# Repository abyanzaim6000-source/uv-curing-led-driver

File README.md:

# Dual-channel UV curing LED driver PCB

A 12 V constant-current driver with two independently PWM-controlled UV outputs. Rev C1 is a routed 110 × 76 mm, four-layer PCB using commercial TI TPS92691 controllers and external power stages. This project closes at the design and simulation stage. Hardware fabrication, measured performance, and curing validation are pending.

| Channel | Power stage | Rev C1 nominal current |
| --- | --- | ---: |
| 365 nm | SEPIC with a 1:1 coupled inductor | 579 mA |
| 405 nm | Boost with upstream TPS26630 eFuse | 501 mA |

*KiCad render. Parts without 3D models appear as footprints.*

## Design decisions

- The 365 nm supply and load voltage ranges call for step-up and step-down operation. Switched modeling showed a growing oscillation with separate inductors and supported selecting the coupled-inductor design.
- The 405 nm output targets a 32–34 V load. Its boost stage includes an eFuse to disconnect the input during a sustained fault.
- Rev C1 uses lower current settings for initial dummy-load bring-up. Modeling also supported increasing the 405 nm soft-start capacitor to 220 nF.

## Files and verification

- [KiCad project](uv_driver/rev_c/UV_DRIVER.kicad_pro), [schematic](uv_driver/rev_c/UV_DRIVER.kicad_sch), and [routed PCB](uv_driver/rev_c/UV_DRIVER.kicad_pcb)
- [Fabrication quote package](results/UV_DRIVER_RevC1_QUOTE_ONLY.zip) with Gerbers, drills, BOM, placements, and KiCad reports
- [Prototype engineering notes](docs/UV_REV_C1_PROTOTYPE.md) and [interview walkthrough](DEMO.md)

| Check | Result |
| --- | --- |
| KiCad 10.0.3 | Zero ERC or DRC violations, unrouted connections, or schematic-to-PCB mismatches |
| 365 nm switched stability screen | No growing mode in 128 modeled operating conditions |
| 405 nm nominal-current transient model | Up to 0.524 A at startup and 0.547 A at PWM restart |

From the project root, run the following with Python 3.9 or later. The SEPIC model requires NumPy.

    python3 scripts/check_uv_sepic_switching.py
    python3 scripts/check_uv_405_restart.py --prototype

The earlier [buck simulation study](docs/LEGACY_BUCK_STUDY.md) and the [development tracker](CODEX_PLAN.md) document the project history. The [bench worksheet](docs/UV_405_BENCH.md) records how the design can be tested later.

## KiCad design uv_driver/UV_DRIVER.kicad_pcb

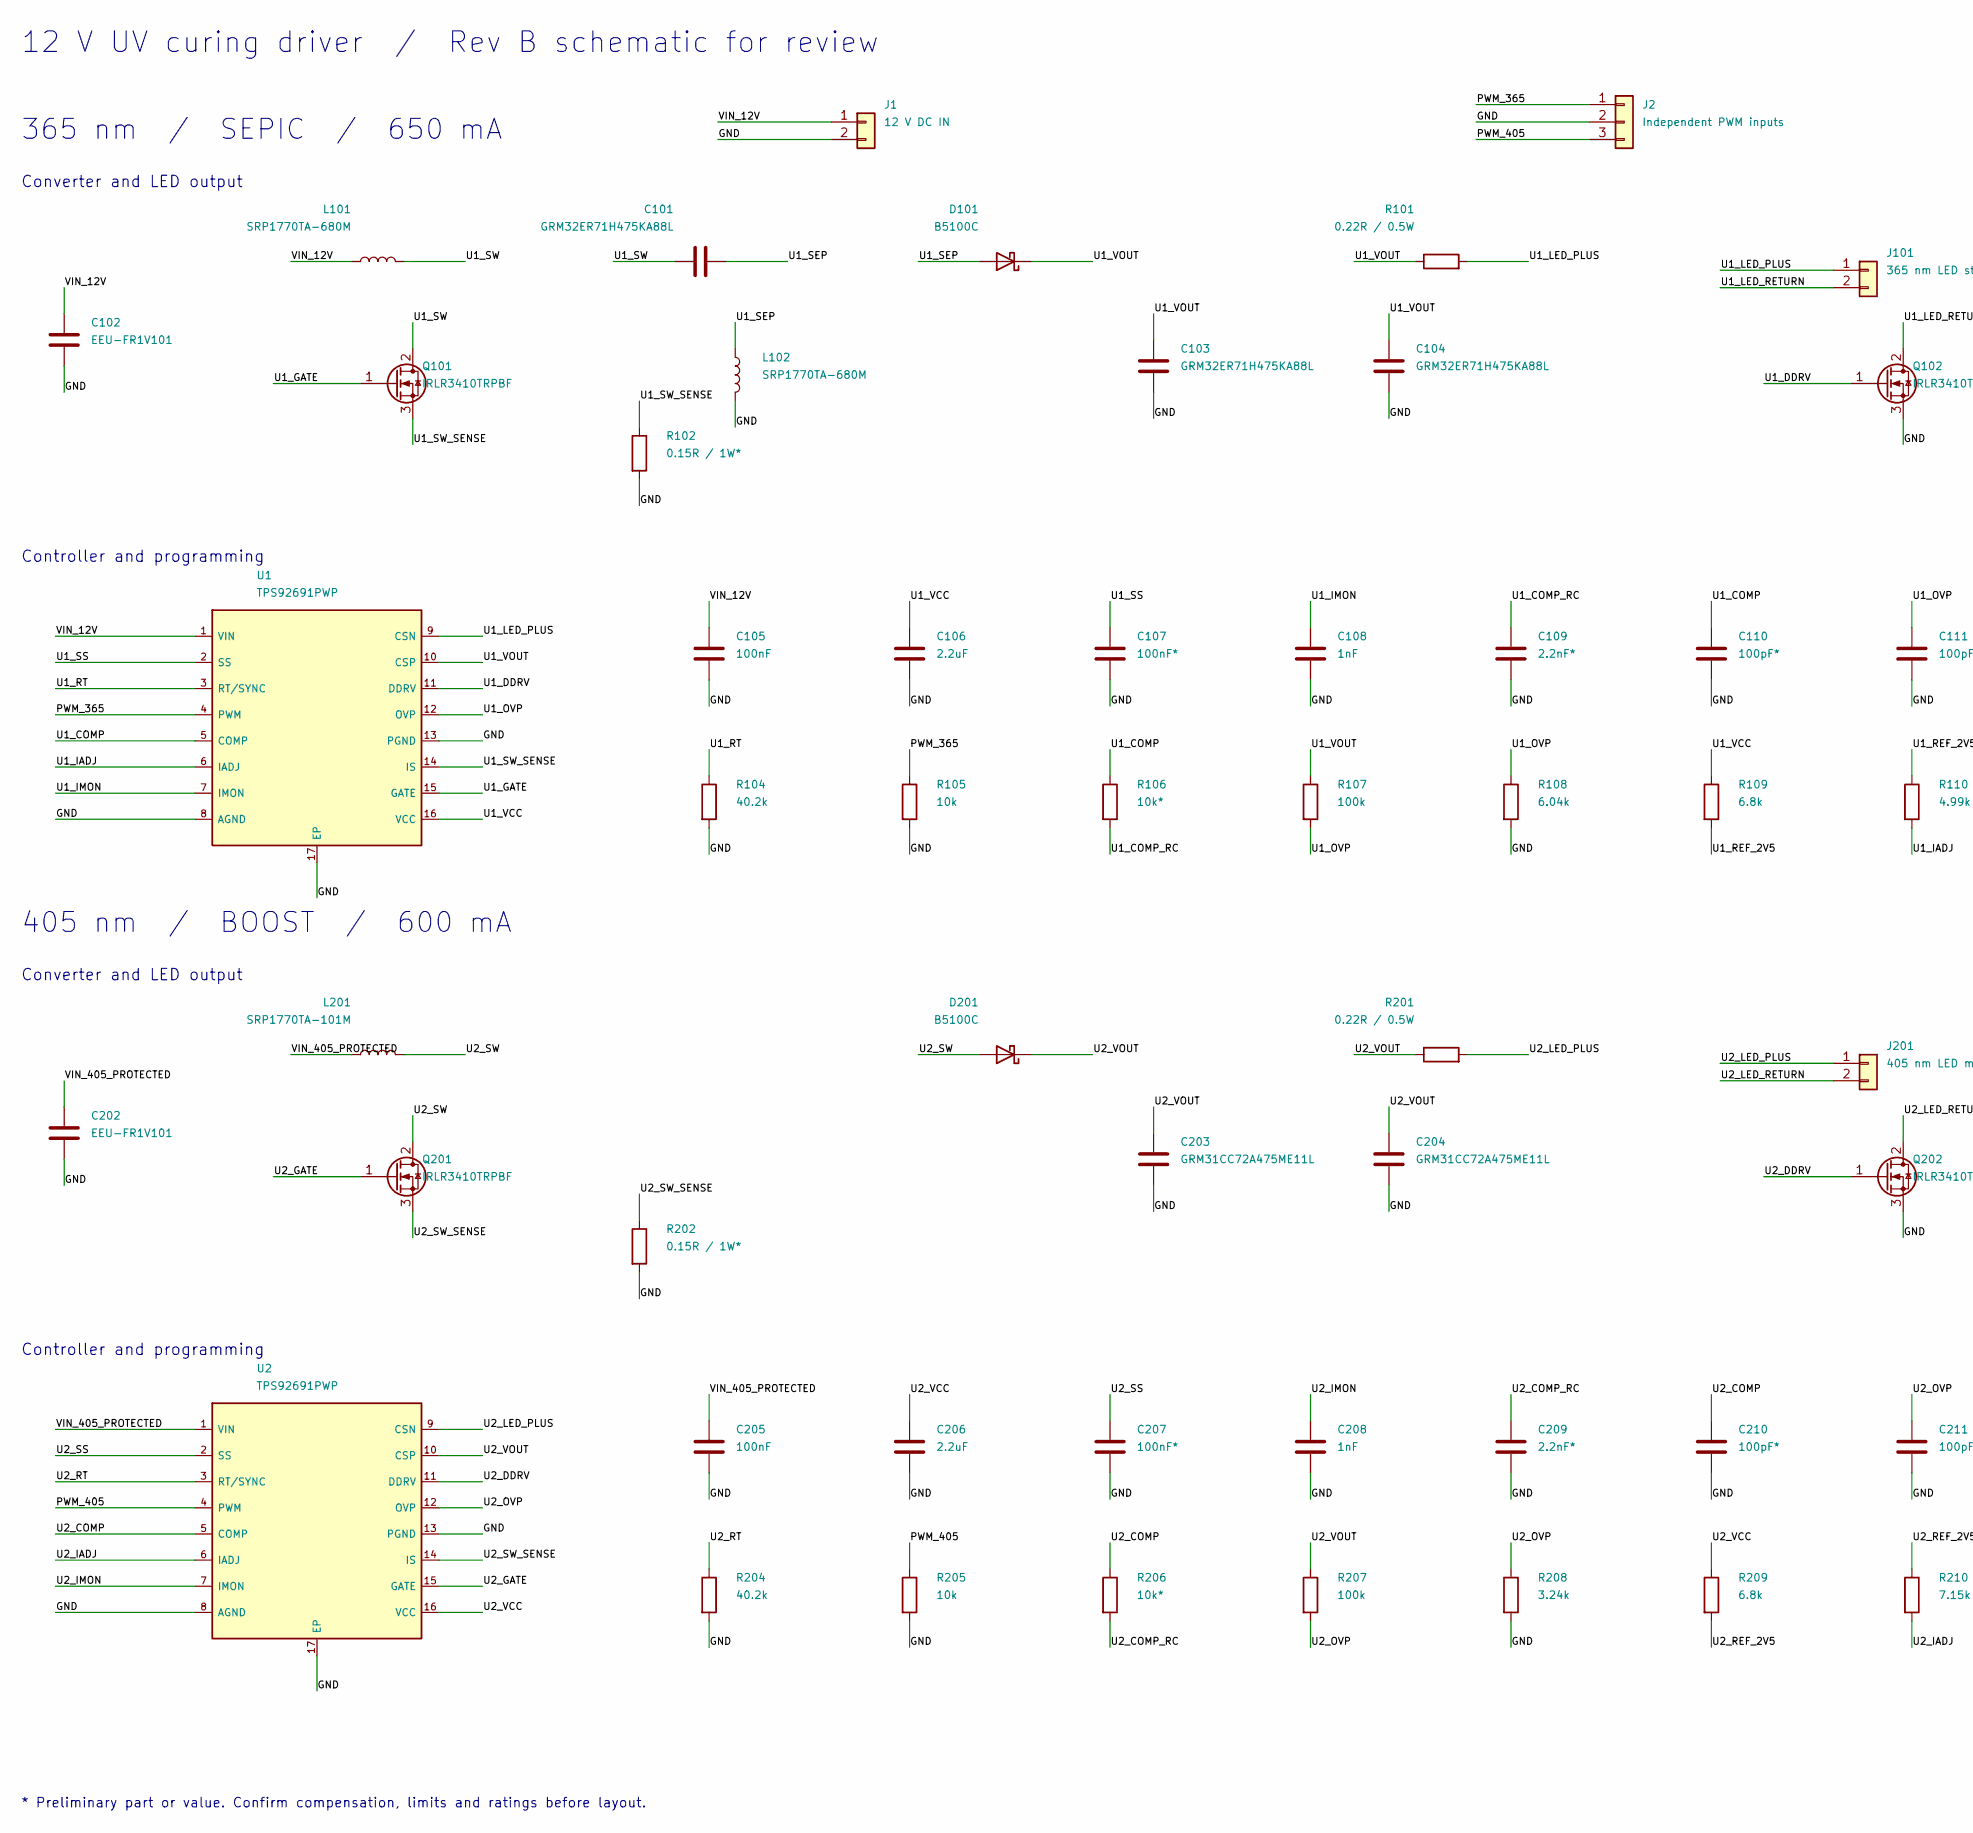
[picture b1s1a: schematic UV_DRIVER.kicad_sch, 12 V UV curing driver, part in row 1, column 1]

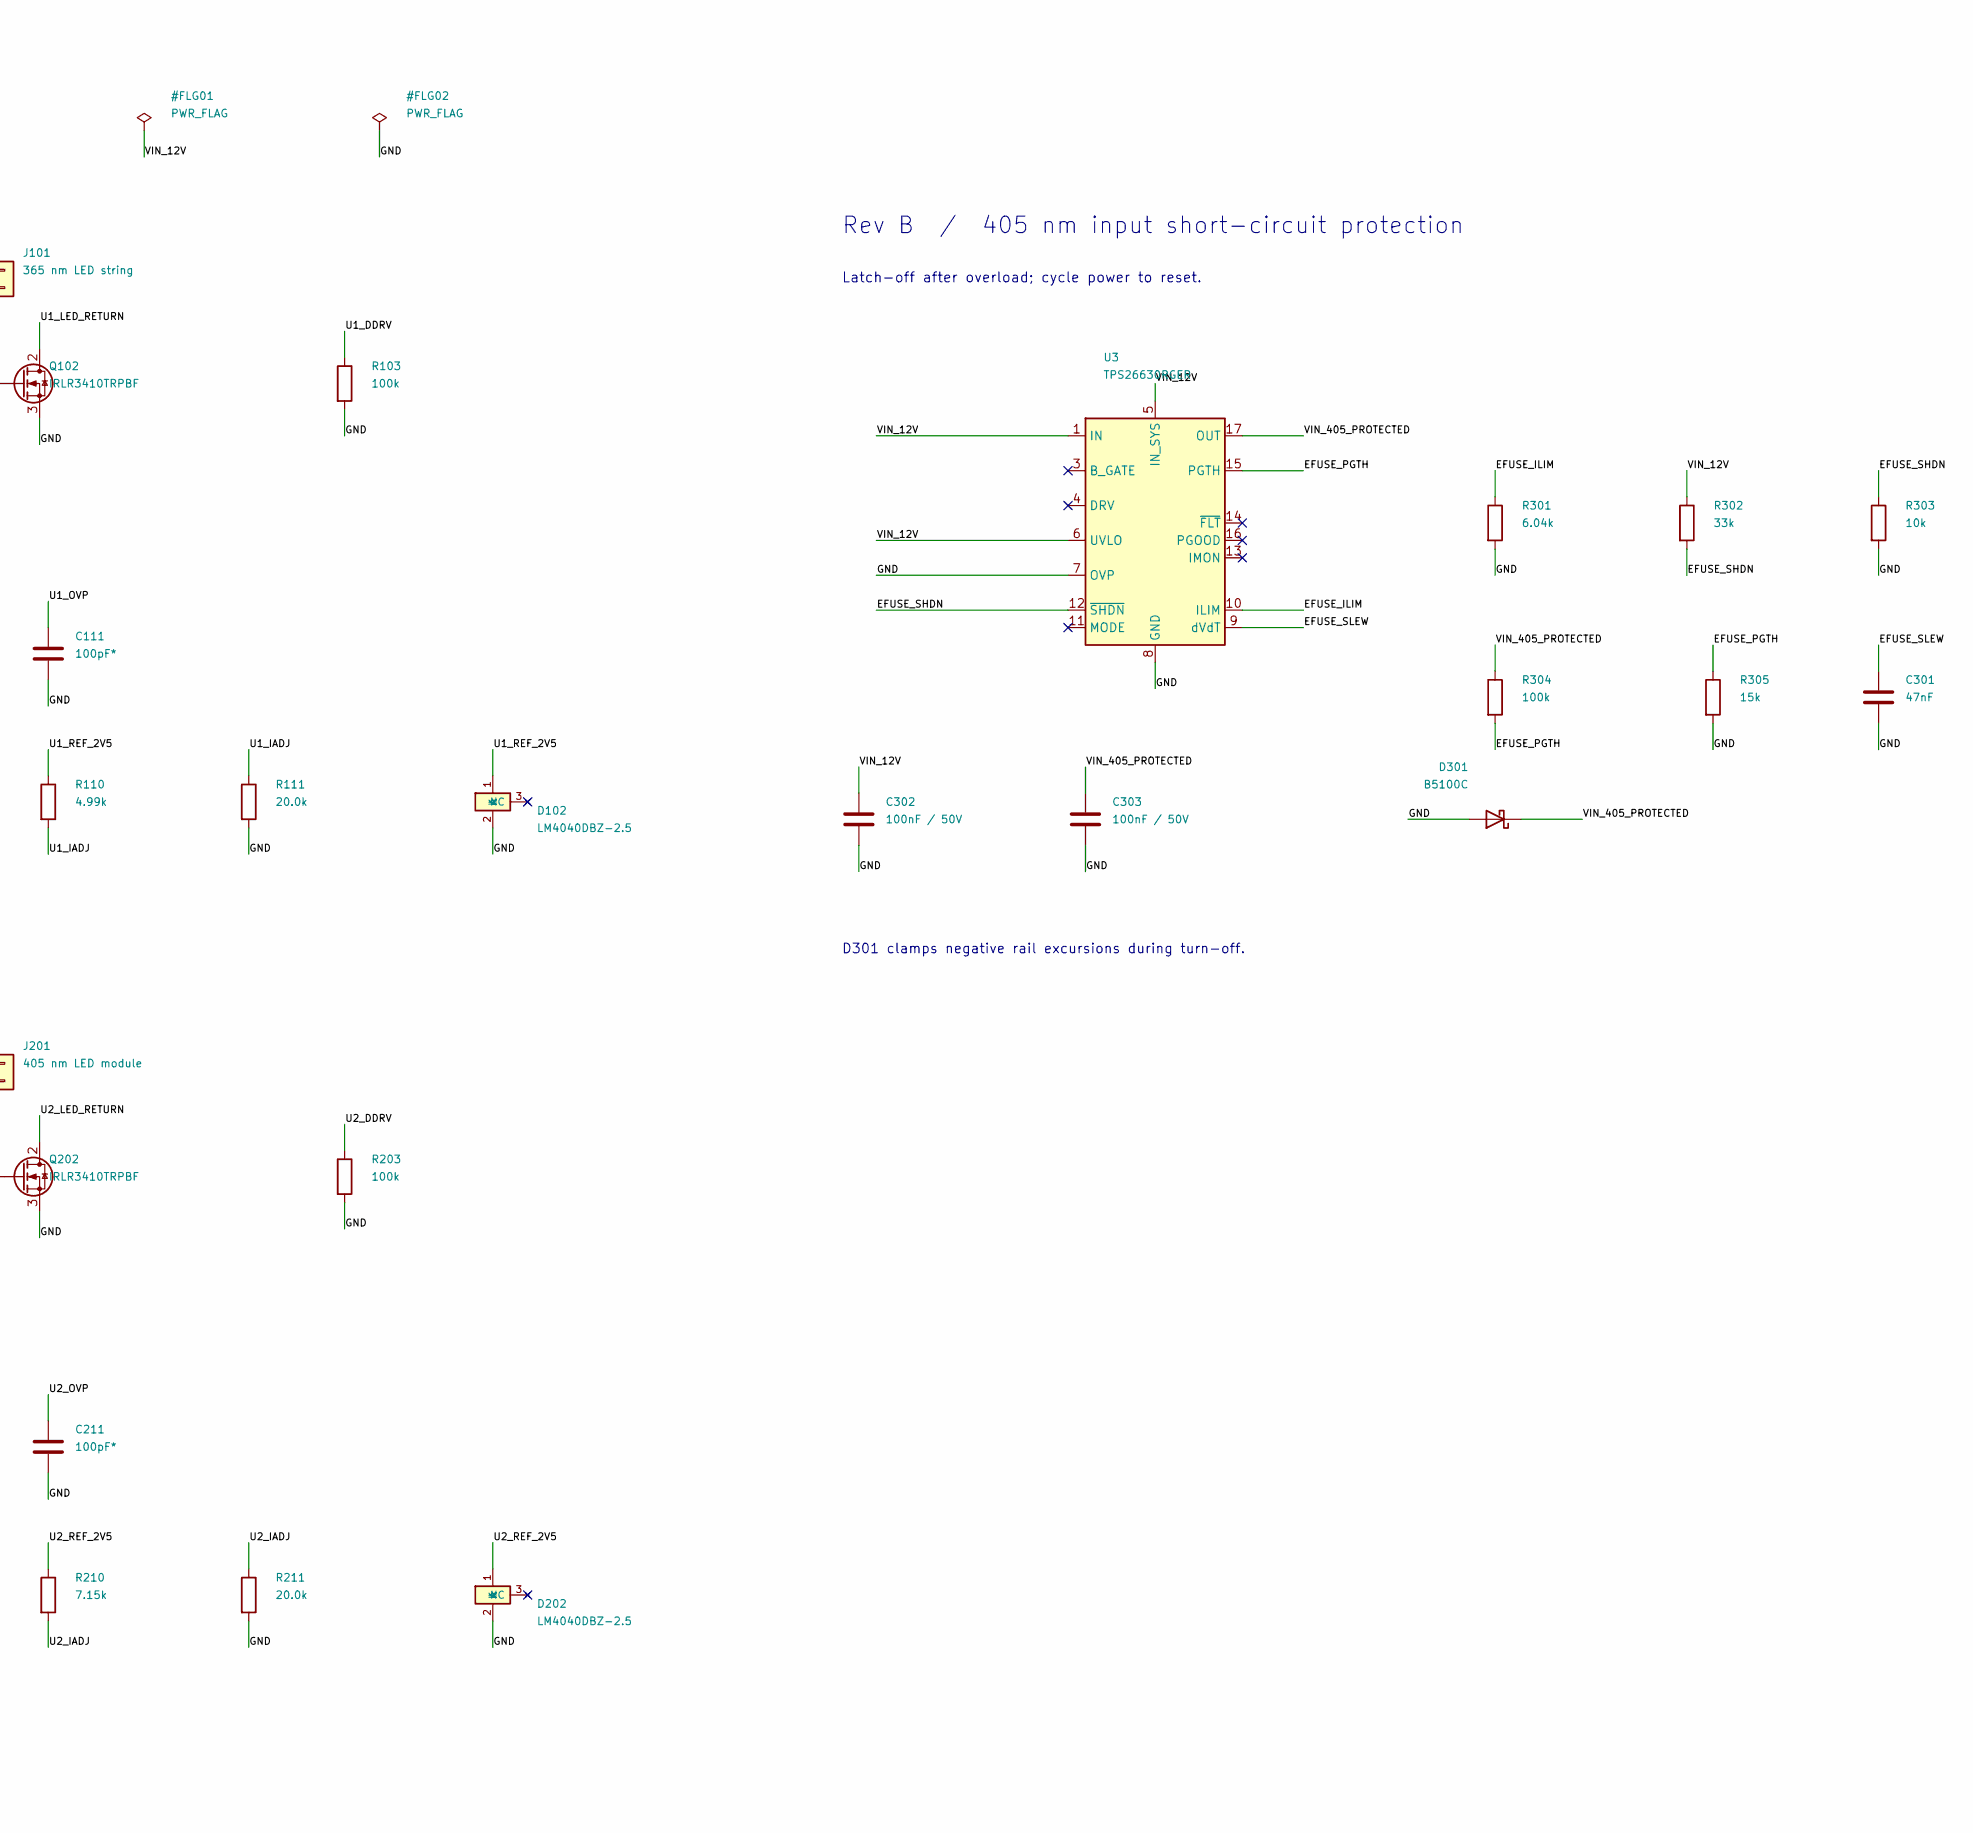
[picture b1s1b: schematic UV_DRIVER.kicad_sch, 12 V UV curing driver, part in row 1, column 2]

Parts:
C101, C103, C104: GRM32ER71H475KA88L; C_1210_3225Metric
C102, C202: EEU-FR1V101; CP_Radial_D8.0mm_P3.50mm
C105, C205: 100nF; C_0603_1608Metric
C106, C206: 2.2uF; C_0603_1608Metric
C107, C207: 100nF*; C_0603_1608Metric
C108, C208: 1nF; C_0603_1608Metric
C109, C209: 2.2nF*; C_0603_1608Metric
C110, C111, C210, C211: 100pF*; C_0603_1608Metric
C203, C204: GRM31CC72A475ME11L; C_1206_3216Metric
C301: 47nF; C_0603_1608Metric
C302, C303: 100nF / 50V; C_0603_1608Metric
D101, D201, D301: B5100C; D_SMC
D102, D202: LM4040DBZ-2.5; SOT-23
J1: 12 V DC IN; TerminalBlock_Phoenix_MKDS-1,5-2-5.08_1x02_P5.08mm_Horizont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
J2: Independent PWM inputs; PinHeader_1x03_P2.54mm_Vertical
J101: 365 nm LED string; TerminalBlock_Phoenix_MKDS-1,5-2-5.08_1x02_P5.08mm_Horizont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
J201: 405 nm LED module; TerminalBlock_Phoenix_MKDS-1,5-2-5.08_1x02_P5.08mm_Horizont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
L101, L102: SRP1770TA-680M; L_Bourns_SRP1770TA_16.9x16.9mm
L201: SRP1770TA-101M; L_Bourns_SRP1770TA_16.9x16.9mm
Q101, Q102, Q201, Q202: IRLR3410TRPBF; TO-252-3_TabPin2
R101, R201: 0.22R / 0.5W; R_1210_3225Metric
R102, R202: 0.15R / 1W*; R_2512_6332Metric
R103, R107, R203, R207, R304: 100k; R_0603_1608Metric
R104, R204: 40.2k; R_0603_1608Metric
R105, R205, R303: 10k; R_0603_1608Metric
R106, R206: 10k*; R_0603_1608Metric
R108, R301: 6.04k; R_0603_1608Metric
R109, R209: 6.8k; R_0603_1608Metric
R110: 4.99k; R_0603_1608Metric
R111, R211: 20.0k; R_0603_1608Metric
R208: 3.24k; R_0603_1608Metric
R210: 7.15k; R_0603_1608Metric
R302: 33k; R_0603_1608Metric
R305: 15k; R_0603_1608Metric
U1, U2: TPS92691PWP; HTSSOP-16-1EP_4.4x5mm_P0.65mm_EP3.4x5mm_Mask2.46x2.31mm
U3: TPS26630RGER; Texas_RGE0024H_VQFN-24-1EP_4x4mm_P0.5mm_EP2.7x2.7mm

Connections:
/EFUSE_ILIM: R301.1, U3.10 (ILIM)
/EFUSE_PGTH: R304.2, R305.1, U3.15 (PGTH)
/EFUSE_SHDN: R302.2, R303.1, U3.12 (~SHDN)
/EFUSE_SLEW: C301.1, U3.9 (dVdT)
/GND: C102.2, C103.2, C104.2, C105.2, C106.2, C107.2, C108.2, C109.2, C110.2, C111.2, C202.2, C203.2, C204.2, C205.2, C206.2, C207.2, C208.2, C209.2, C210.2, C211.2, C301.2, C302.2, C303.2, D102.2 (A), D202.2 (A), D301.2 (A), J1.2, J2.2, L102.2, Q102.3 (S), Q202.3 (S), R102.2, R103.2, R104.2, R105.2, R108.2, R111.2, R202.2, R203.2, R204.2, R205.2, R208.2, R211.2, R301.2, R303.2, R305.2, U1.8 (AGND), U1.13 (PGND), U1.17 (EP), U2.8 (AGND), U2.13 (PGND), U2.17 (EP), U3.7 (OVP), U3.8 (GND), U3.25 (GND)
/PWM_365: J2.1, R105.1, U1.4 (PWM)
/PWM_405: J2.3, R205.1, U2.4 (PWM)
/U1_COMP: C110.1, R106.1, U1.5 (COMP)
/U1_COMP_RC: C109.1, R106.2
/U1_DDRV: Q102.1 (G), R103.1, U1.11 (DDRV)
/U1_GATE: Q101.1 (G), U1.15 (GATE)
/U1_IADJ: R110.2, R111.1, U1.6 (IADJ)
/U1_IMON: C108.1, U1.7 (IMON)
/U1_LED_PLUS: J101.1, R101.2, U1.9 (CSN)
/U1_LED_RETURN: J101.2, Q102.2 (D)
/U1_OVP: C111.1, R107.2, R108.1, U1.12 (OVP)
/U1_REF_2V5: D102.1 (K), R109.2, R110.1
/U1_RT: R104.1, U1.3 (RT/SYNC)
/U1_SEP: C101.2, D101.2 (A), L102.1
/U1_SS: C107.1, U1.2 (SS)
/U1_SW: C101.1, L101.2, Q101.2 (D)
/U1_SW_SENSE: Q101.3 (S), R102.1, U1.14 (IS)
/U1_VCC: C106.1, R109.1, U1.16 (VCC)
/U1_VOUT: C103.1, C104.1, D101.1 (K), R101.1, R107.1, U1.10 (CSP)
/U2_COMP: C210.1, R206.1, U2.5 (COMP)
/U2_COMP_RC: C209.1, R206.2
/U2_DDRV: Q202.1 (G), R203.1, U2.11 (DDRV)
/U2_GATE: Q201.1 (G), U2.15 (GATE)
/U2_IADJ: R210.2, R211.1, U2.6 (IADJ)
/U2_IMON: C208.1, U2.7 (IMON)
/U2_LED_PLUS: J201.1, R201.2, U2.9 (CSN)
/U2_LED_RETURN: J201.2, Q202.2 (D)
/U2_OVP: C211.1, R207.2, R208.1, U2.12 (OVP)
/U2_REF_2V5: D202.1 (K), R209.2, R210.1
/U2_RT: R204.1, U2.3 (RT/SYNC)
/U2_SS: C207.1, U2.2 (SS)
/U2_SW: D201.2 (A), L201.2, Q201.2 (D)
/U2_SW_SENSE: Q201.3 (S), R202.1, U2.14 (IS)
/U2_VCC: C206.1, R209.1, U2.16 (VCC)
/U2_VOUT: C203.1, C204.1, D201.1 (K), R201.1, R207.1, U2.10 (CSP)
/VIN_12V: C102.1, C105.1, C302.1, J1.1, L101.1, R302.1, U1.1 (VIN), U3.1 (IN), U3.2 (IN), U3.5 (IN_SYS), U3.6 (UVLO)
/VIN_405_PROTECTED: C202.1, C205.1, C303.1, D301.1 (K), L201.1, R304.1, U2.1 (VIN), U3.17 (OUT), U3.18 (OUT)

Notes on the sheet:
12 V UV curing driver / Rev B schematic for review
365 nm / SEPIC / 650 mA
Converter and LED output
Controller and programming
405 nm / BOOST / 600 mA
* Preliminary part or value. Confirm compensation, limits and ratings before layout.
Rev B / 405 nm input short-circuit protection
Latch-off after overload; cycle power to reset.
D301 clamps negative rail excursions during turn-off.

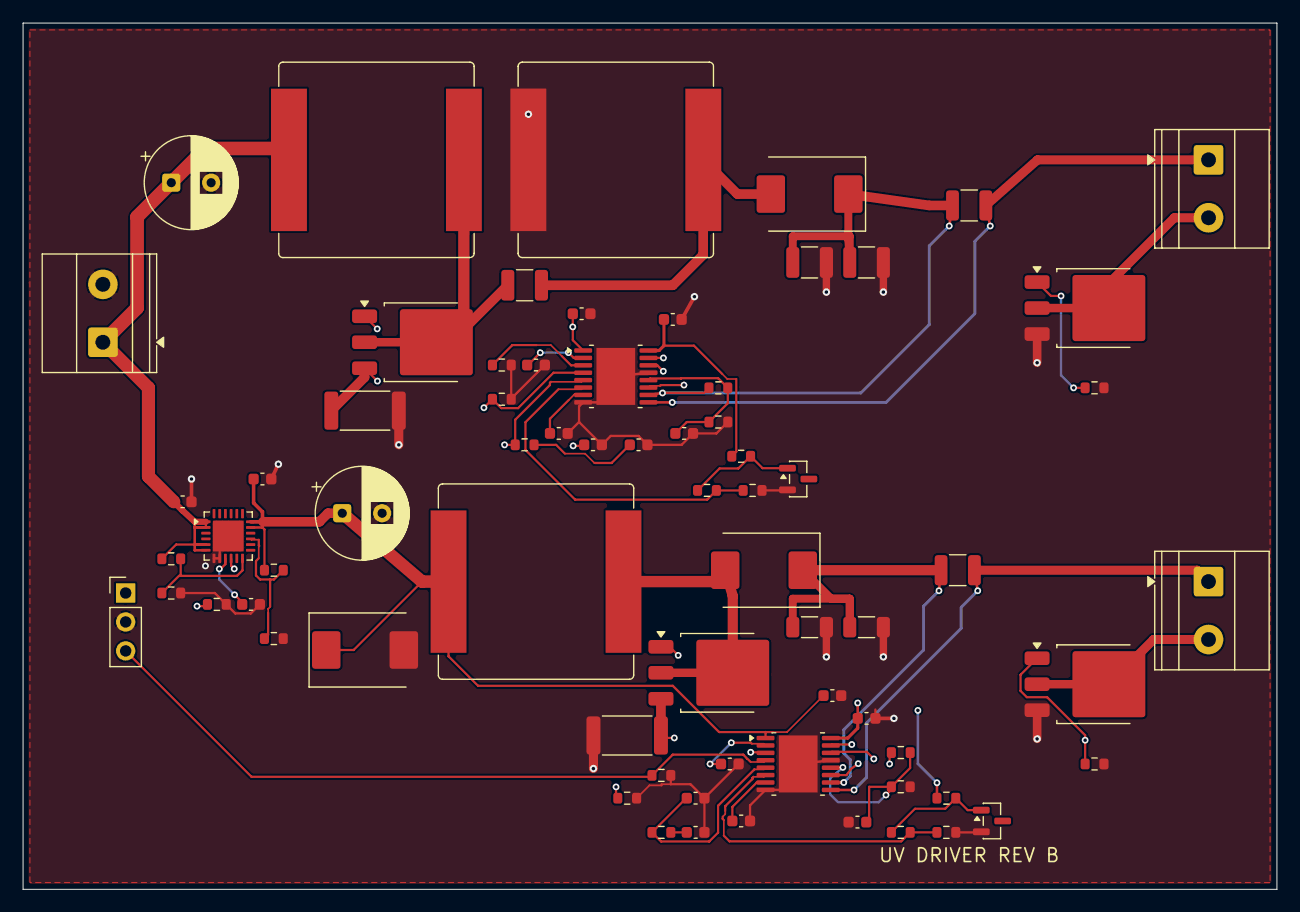
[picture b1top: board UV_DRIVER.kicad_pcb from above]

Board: 4 copper layers, 110.0 x 76.0 mm, 70 parts (0 on the bottom side), 42 nets.

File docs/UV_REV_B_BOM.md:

# Rev B prototype sourcing review

Use this list to prepare a cart and review substitutions. Quantities are per board and exclude spares. The existing [quote archive](../results/UV_DRIVER_RevB_QUOTE_ONLY.zip) remains the reference for placement and footprint data. Release of the prototype order requires the checks below. Stock, pricing and assembler-approved substitutes are pending.

**Follow-up review:** The [engineering review](UV_REV_B_ENGINEERING_REVIEW.md) supersedes the initial switch-shunt and compensation carry-forward decisions. Keep those parts and the output-capacitor banks on hold for the next design revision.

## Board BOM

Generic resistors are 0603, 1%, ≥0.1 W at rated conditions, ≤100 ppm/°C and ≥50 V working voltage unless specified otherwise. Generic capacitors are 0603 and ±10% unless specified. Verify the chosen manufacturer's land pattern, derating and availability before locking the cart.

| References | Qty | Candidate or minimum specification | Review |
| --- | ---: | --- | --- |
| C101, C103, C104 | 3 | Murata GRM32ER71H475KA88L, 4.7 µF, 50 V X7R, 1210 | Check coupling-capacitor RMS current and effective capacitance under bias. |
| C102, C202 | 2 | Panasonic EEU-FR1V101, 100 µF, 35 V, radial Ø8 mm, 3.5 mm pitch | Check input ripple and polarity. Through-hole. |
| C105, C205, C302, C303 | 4 | 100 nF, 50 V X7R | Generic. |
| C106, C206 | 2 | 2.2 µF, ≥16 V X7R | VCC bypass. Check effective capacitance near 7.5 V and consider a 4.7 µF candidate in the same footprint if needed. |
| C107, C207 | 2 | 100 nF, 50 V X7R | Provisional soft-start population. |
| C108, C208 | 2 | 1 nF, 50 V C0G | Generic. |
| C109, C209 | 2 | 2.2 nF, 50 V C0G | COMP tuning. |
| C110, C210 | 2 | 100 pF, 50 V C0G | COMP tuning. |
| C111, C211 | 2 | 100 pF, 50 V C0G | Provisional OVP filter population. |
| C203, C204 | 2 | Murata GRM31CC72A475ME11L, 4.7 µF, 100 V X7S, 1206 | Check effective capacitance across normal load and OVP voltages. |
| C301 | 1 | 47 nF, 50 V X7R | Verify eFuse startup with the boost input bulk capacitor. |
| D101, D201, D301 | 3 | Diodes Inc. B5100C family, 100 V, 5 A Schottky, SMC | Confirm exact packaging suffix. Review rectifier heat and eFuse clamp pulse. |
| D102, D202 | 2 | Texas Instruments LM4040B25IDBZR, 2.5 V, SOT-23 | DBZ pin 1 cathode, pin 2 anode, pin 3 floating or tied to anode per TI. Rev B leaves pin 3 floating. |
| J1, J101, J201 | 3 | Phoenix Contact 1715721, 2 positions, 5.08 mm pitch, horizontal wire entry | Through-hole. Check wire access in the enclosure. |
| J2 | 1 | Samtec TSW-103-07-G-S, 1×3 straight 2.54 mm header | Through-hole. Include mating cable in the bench kit. |
| L101, L102 | 2 | Bourns SRP1770TA-680M, 68 µH | Check hot saturation headroom and copper loss. |
| L201 | 1 | Bourns SRP1770TA-101M, 100 µH | Check saturation and heating at the high trip corner. |
| Q101, Q102, Q201, Q202 | 4 | Infineon IRLR3410TRPBF, 100 V, DPAK | Check switching loss, heat and overshoot margin. |
| R101, R201 | 2 | 0.22 Ω, 1%, 1210, ≥0.5 W. Candidate Vishay RCWE1210R220FKEA | LED current sensing. Review TCR and pad layout. |
| R102, R202 | 2 | 0.15 Ω, 1%, 2512, 1 W. Candidate Vishay WSL2512R1500FEA | Provisional switch shunt. Check pulse load and copper temperature. |
| R103, R107, R203, R207, R304 | 5 | 100 kΩ | Generic. |
| R104, R204 | 2 | 40.2 kΩ | Generic. |
| R105, R205, R303 | 3 | 10 kΩ | Generic. |
| R106, R206 | 2 | 10 kΩ | COMP tuning. |
| R108, R301 | 2 | 6.04 kΩ | Generic. |
| R109, R209 | 2 | 6.8 kΩ | Generic. |
| R110 | 1 | 4.99 kΩ | Generic. |
| R111, R211 | 2 | 20.0 kΩ | Generic. |
| R208 | 1 | 3.24 kΩ | Generic. |
| R210 | 1 | 7.15 kΩ | Generic. |
| R302 | 1 | 33 kΩ | Generic. |
| R305 | 1 | 15 kΩ | Generic. |
| U1, U2 | 2 | Texas Instruments TPS92691PWP, HTSSOP-16 exposed pad | Review stencil and thermal-pad assembly. |
| U3 | 1 | Texas Instruments TPS26630RGER, VQFN-24 exposed pad | Review stencil and thermal-pad assembly. |

70 placements total, including 64 SMT and six through-hole. See the [power-stage notes](UV_POWER_STAGE.md) for the principal power-component datasheets. [TI LM4040 datasheet](https://www.ti.com/lit/ds/symlink/lm4040.pdf), [Samtec header](https://www.samtec.com/products/tsw-103-07-g-s), [Phoenix terminal block](https://www.phoenixcontact.com/gb/products/1715721), [Vishay RCWE](https://www.vishay.com/docs/20019/rcwe.pdf), [Vishay WSL](https://www.vishay.com/docs/30100/wsl.pdf).

## Review of the 12 starred placements

| References | First-article decision | Release or test condition |
| --- | --- | --- |
| C107, C207 | Retain 100 nF as the starting soft-start value. TI uses 100 nF in a reference design with an approximately 8 ms target. | Check startup current and overshoot with PWM high and low. Rev B's total ramp depends on the converters, load and eFuse behavior. |
| C111, C211 | Retain 100 pF C0G as the starting OVP filter. Divider Thévenin resistance gives approximately 0.57 µs at 365 nm and 0.31 µs at 405 nm, ignoring parasitics. | Calculate transient headroom against OVP threshold spread and check trip, overshoot and restart with an open load. |
| R102, R202 | Retain 0.15 Ω, 1%, 1 W as the starting switch shunt. The comparator and resistor tolerances give a 3.28–3.70 A static trip range. | Screening gives approximately 0.29 W SEPIC and 0.51 W boost in normal steady operation using the estimated input currents, duty and inductor ripple. About 2 W can occur instantaneously at the upper trip. Review pulse curves, current-limit delay, hot derating and fault repetition. |
| R106, R206, C109, C209, C110, C210 | Keep 10 kΩ, 2.2 nF and 100 pF as tuning candidates for each channel. These values give a network zero near 7.2 kHz and a high-frequency pole near 166 kHz. | Estimate crossover and phase margin separately for SEPIC and boost. Use vendor capacitance under DC bias, measured or bounded LED incremental resistance and topology-specific right-half-plane zeros. Plan bench tuning and stock only the alternatives justified by the analysis. |

The nominal current settings from the IADJ dividers and 0.22 Ω shunts are approximately 650 mA and 598 mA. The steady shunt dissipation is approximately 93 mW and 79 mW. Emitters still need a current and thermal envelope that includes ripple, tolerance and hot operating conditions. The existing behavioral simulation can screen power-stage behavior and the test sequence. Loop stability with the actual controller and load remains open. [TI TPS92691 datasheet](https://www.ti.com/lit/ds/symlink/tps92691.pdf).

## Before ordering and after delivery

1. Before paying for fabrication, close the on-paper compensation, capacitor, electrical stress and PCB layout review. Check package dimensions, availability, and the manufacturer’s four-layer stackup, drills and exposed-pad assembly process. Freeze one revision and export matching fabrication and assembly files after the final KiCad checks.
2. Budget separately for the four Broadcom AUV3-SQ62-0RT0K emitters and a TaoYuan TY-405nm20W sample, heatsinking, wiring, plus access to a current-limited bench supply, dummy load and measurement tools. Close the module bin and temperature limits before using it at target current. See the [405 nm bench worksheet](UV_405_BENCH.md).
3. Buy components and submit a small prototype fabrication order when budget permits and the release checks pass. After assembly, verify startup, regulation, PWM, fault behavior and temperatures on dummy loads first. Use a shielded, appropriately cooled setup for UV emitter tests.
